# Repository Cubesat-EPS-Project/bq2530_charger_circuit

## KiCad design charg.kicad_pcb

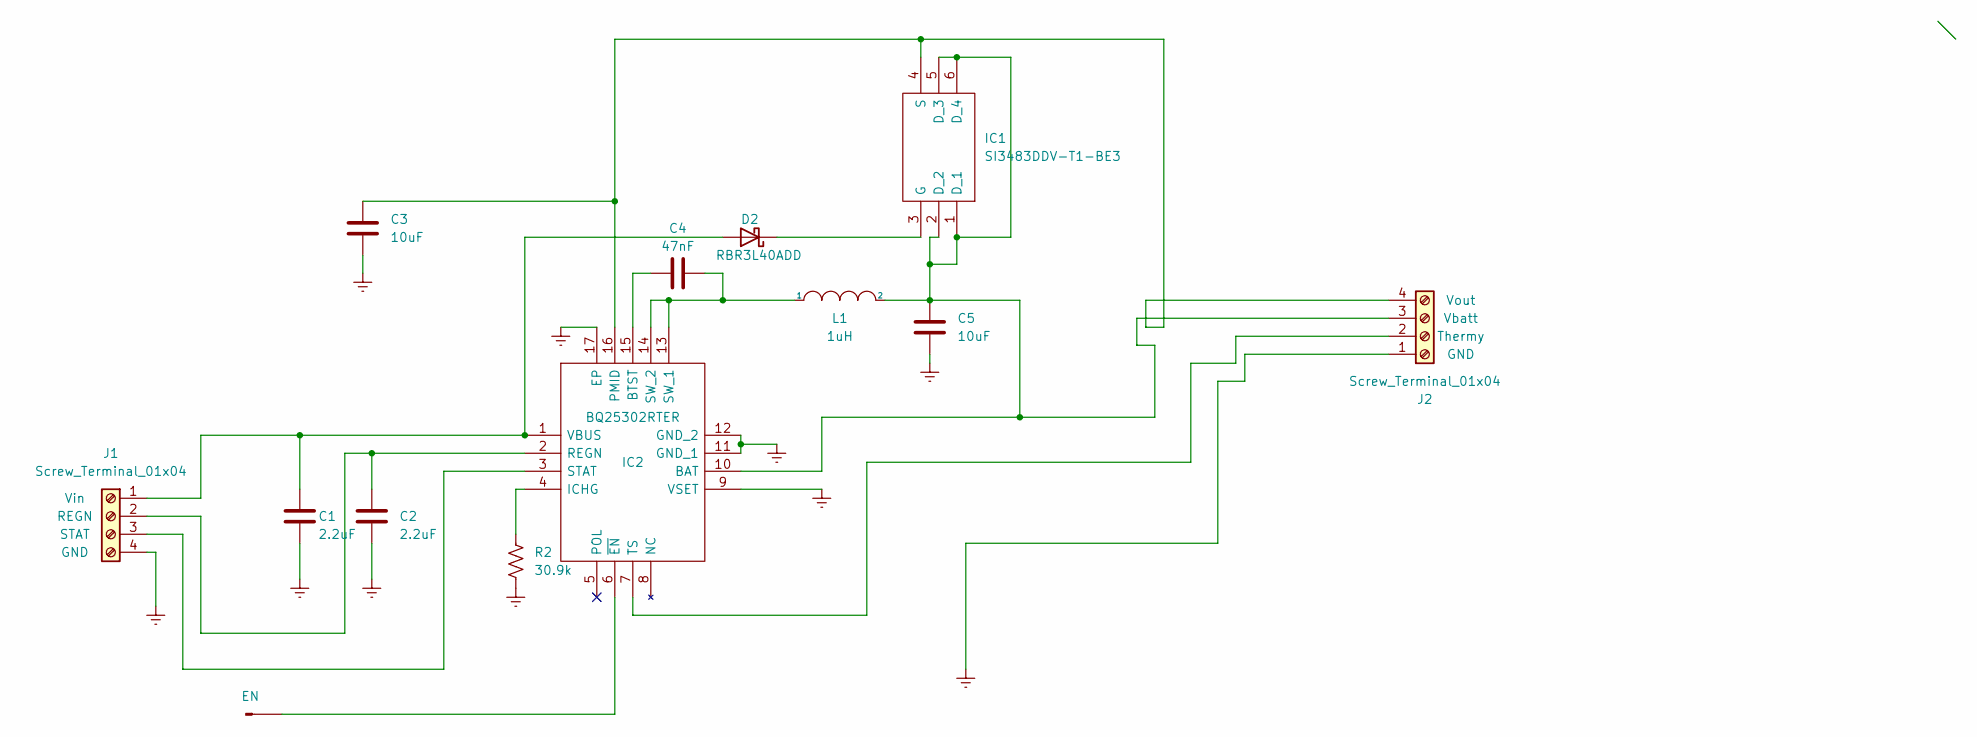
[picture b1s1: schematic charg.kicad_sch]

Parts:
C1, C2: 2.2uF; CAPC0603X33N
C3, C5: 10uF; CAPC2012X94N
C4: 47nF; C1005_Commercial
D2: RBR3L40ADD; DIOM5126X265N
IC1: SI3483DDV-T1-BE3; SOT95P284X110-6N; Mouser Part Number 78-SI3483DDV-T1-BE3
IC2: BQ25302RTER; QFN50P300X300X80-17N-D; Mouser Part Number 595-BQ25302RTER
J1, J2: Screw_Terminal_01x04; TerminalBlock_MetzConnect_Type059_RT06304HBWC_1x04_P3.50mm_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
J4: EN; PinHeader_1x01_P1.00mm_Vertical
L1: 1uH; IHHP0805ZHER1R0M01
R2: 30.9k; RC0603FR-0730K9L

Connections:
Earth: C1.2, C2.2, C3.2, C5.2, IC2.9 (VSET), IC2.11 (GND_1), IC2.12 (GND_2), IC2.17 (EP), J1.4, J2.1, R2.1
unnamed: C1.1, D2.2 (A), IC2.1 (VBUS), J1.1
unnamed: C2.1, IC2.2 (REGN), J1.2
unnamed: C3.1, IC1.4 (S), IC2.16 (PMID), J2.4
unnamed: C4.1, IC2.15 (BTST)
unnamed: C4.2, IC2.13 (SW_1), IC2.14 (SW_2), L1.1
unnamed: C5.1, IC1.1 (D_1), IC1.2 (D_2), IC1.5 (D_3), IC1.6 (D_4), IC2.10 (BAT), J2.3, L1.2
unnamed: D2.1 (K), IC1.3 (G)
unnamed: IC2.3 (STAT), J1.3
unnamed: IC2.4 (ICHG), R2.2
unnamed: IC2.6 (~EN), J4.1
unnamed: IC2.7 (TS), J2.2

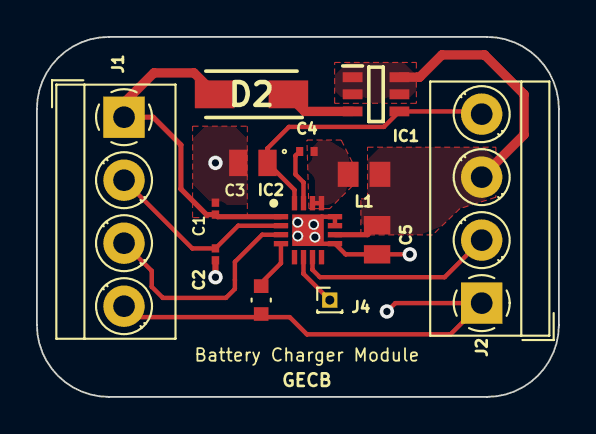
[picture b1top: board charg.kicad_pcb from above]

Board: 2 copper layers, 29.0 x 20.0 mm, 13 parts (0 on the bottom side), 12 nets.

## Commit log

2023-01-14 INIT - Schematic Done
2023-01-15 fixes
2023-01-25 Major schematic edit
    Thermy and STAT LED should be connected externally. Assigned FPs.
2023-01-25 Patches + PCB start
2023-01-25 Libs and 3D exported
2023-01-25 Debloat
2023-01-26 Patch
2023-01-27 No idea
2023-01-29 PCB v1
2023-01-30 fill
    filled earth
2023-02-01 Patches + Fixes
2023-02-05 Chamfer'd
2023-02-10 DRC chk n' fix
2023-02-10 FInal...I guess
2023-02-13 Replace 30k ISEt with 30.9k
2023-02-13 Update Gerbuhs
2023-02-13 Libs update
2023-02-22 Sch cleanup
2023-05-08 Add thermy rsts
2023-05-22 Test-board schematic start and module symbol creation

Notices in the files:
parts and their libraries:
Copyright 2021 Accelerated Designs. All rights reserved.
